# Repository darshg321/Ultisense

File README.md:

# Ultisense

an esp32-s3 devboard made to sense as many things as possible

has:
- an NFC antenna
- 6DOF IMU
- VOC air sensor
- humidity & temperature sensor
- color & ambient light sensor
- magnetometer

it additionally has:
- microphone
- two speakers
- microSD card

## BOM

|Item|Qty                                        |Price (USD)                                |
|----|-------------------------------------------|-------------------------------------------|
|PCB |5                                          |4                                          |
|PCBA|2                                          |161.91                                     |
|Shipping (GSDL)|                                |12.36                                      |

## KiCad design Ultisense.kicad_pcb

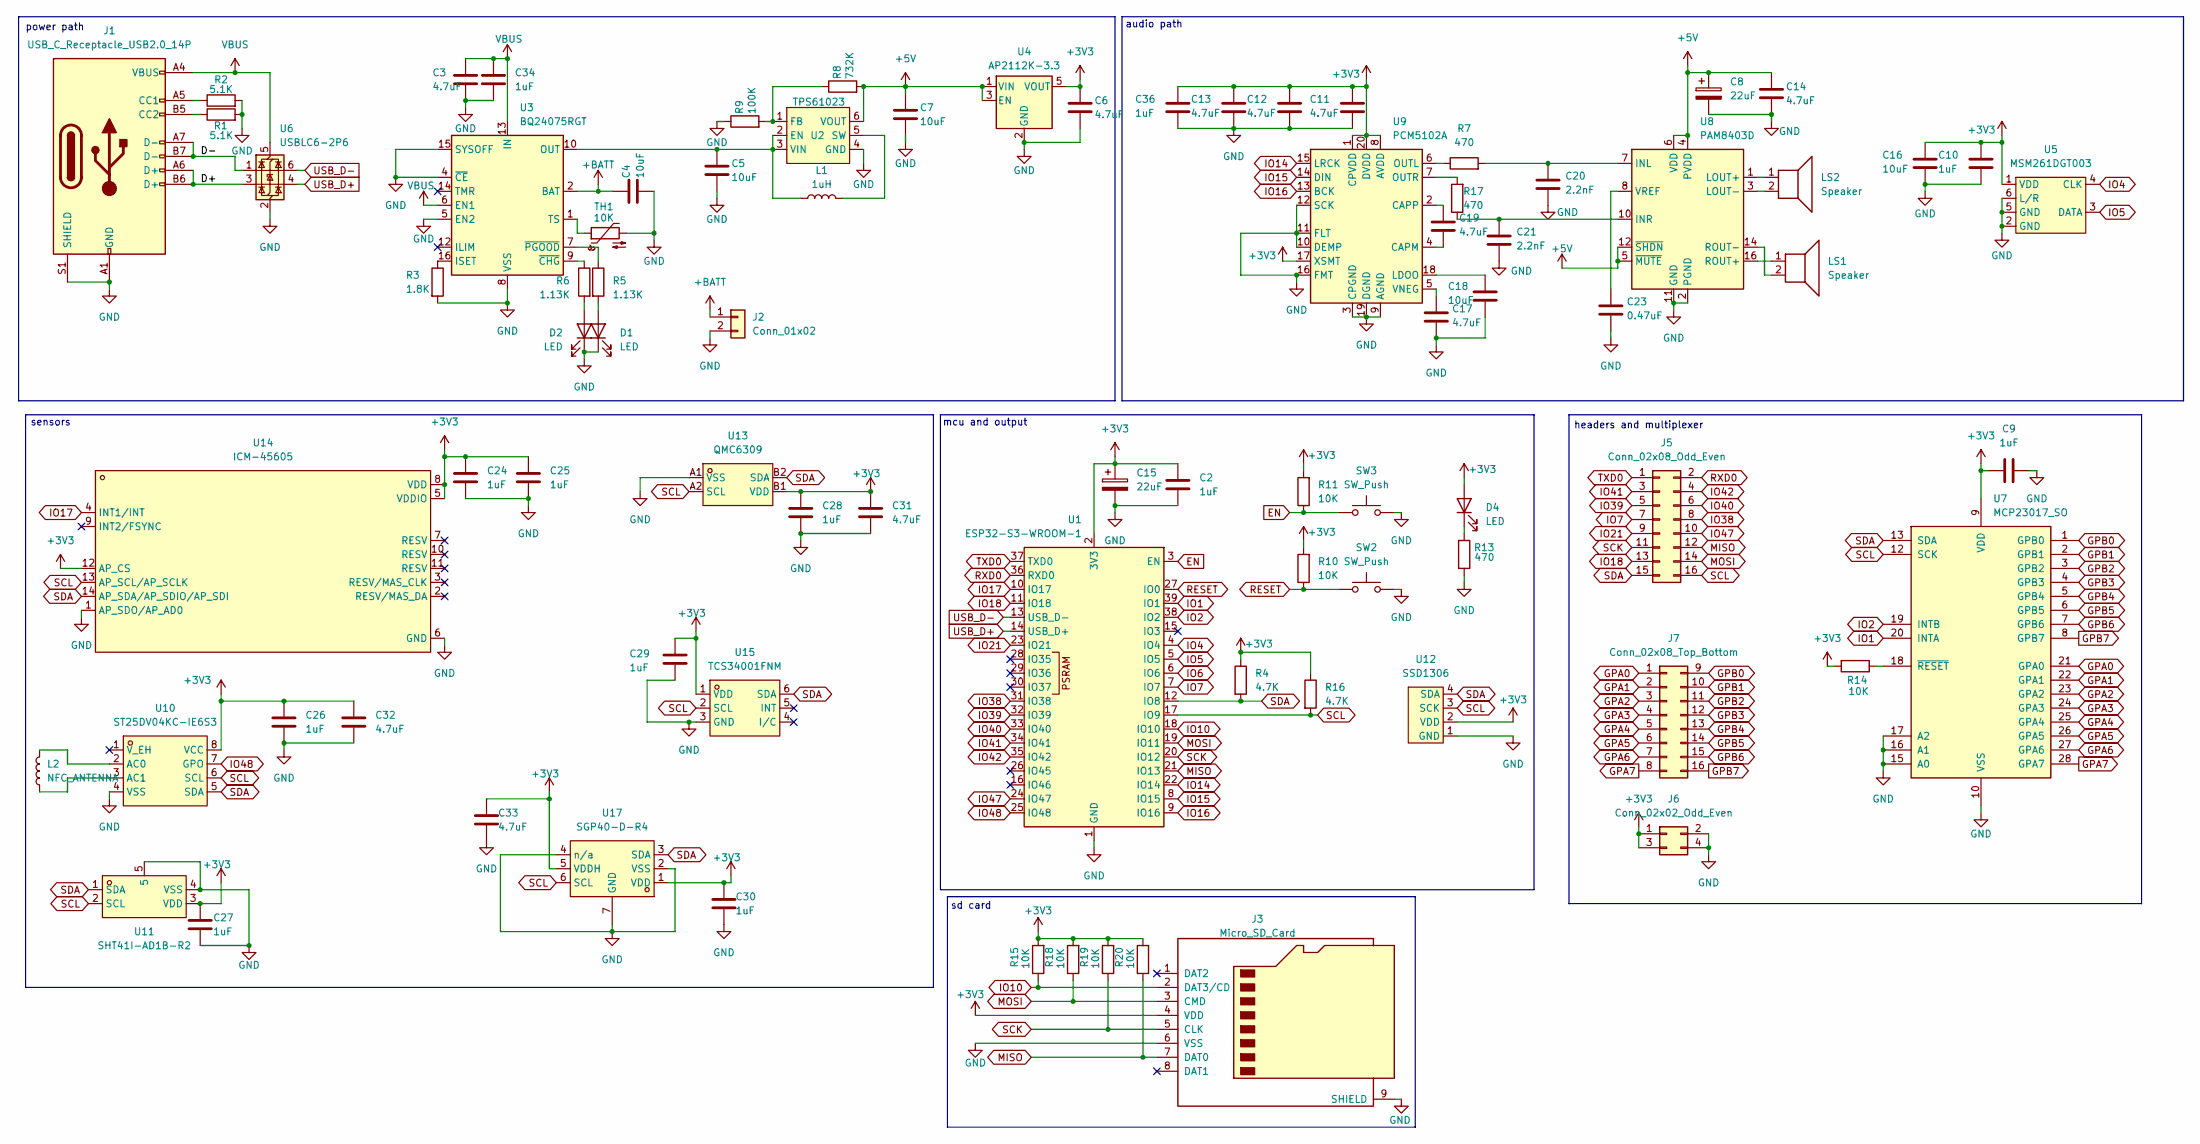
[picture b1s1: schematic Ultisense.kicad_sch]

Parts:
C2, C9, C10, C24, C25, C26, C27, C28, C29, C30, C34, C36: 1uF; C_0201_0603Metric
C3, C6, C11, C12, C13, C14, C17, C19, C31, C32, C33: 4.7uF; C_0201_0603Metric
C4, C5, C7, C16, C18: 10uF; C_0603_1608Metric
C8, C15: 22uF; CP_Elec_4x5.4
C20, C21: 2.2nF; C_0402_1005Metric
C23: 0.47uF; C_0402_1005Metric
D1, D2, D4: LED; LED_0603_1608Metric
J1: USB_C_Receptacle_USB2.0_14P; USB_C_Receptacle_HRO_TYPE-C-31-M-12
J2: Conn_01x02; PinHeader_1x02_P2.54mm_Vertical
J3: Micro_SD_Card; TF-SMD_TF-PUSH
J5: Conn_02x08_Odd_Even; PinHeader_2x08_P2.54mm_Vertical
J6: Conn_02x02_Odd_Even; PinHeader_2x02_P2.54mm_Vertical
J7: Conn_02x08_Top_Bottom; PinSocket_2x08_P2.54mm_Vertical
L1: 1uH; IND-SMD_L4.0-W4.0-A
L2: NFC_ANTENNA; NFC_Coil
LS1, LS2: Speaker; PinHeader_2x01_P2.54mm_Vertical
R1, R2: 5.1K; R_0201_0603Metric
R3: 1.8K; R_0201_0603Metric
R4, R16: 4.7K; R_0201_0603Metric
R5, R6: 1.13K; R_0201_0603Metric
R7, R13, R17: 470; R_0201_0603Metric
R8: 732K; R_0201_0603Metric
R9: 100K; R_0201_0603Metric
R10, R11, R14, R15, R18, R19, R20: 10K; R_0201_0603Metric
SW2, SW3: SW_Push; SW-SMD_L3.9-W3.0-P4.45
TH1: 10K; R_0603_1608Metric
U1: ESP32-S3-WROOM-1
U2: TPS61023; SOT-563_L1.6-W1.2-P0.50-LS1.6-BR
U3: BQ24075RGT; VQFN-16-1EP_3x3mm_P0.5mm_EP1.6x1.6mm
U4: AP2112K-3.3; SOT-23-5
U5: MSM261DGT003; MIC-SMD_6P-L4.0-W2.0_LMD4020T261-OC3
U6: USBLC6-2P6; SOT-666
U7: MCP23017_SO; SOIC-28W_7.5x17.9mm_P1.27mm
U8: PAM8403D; SOP-16_3.9x9.9mm_P1.27mm
U9: PCM5102A; TSSOP-20_4.4x6.5mm_P0.65mm
U10: ST25DV04KC-IE6S3; SO-8_L4.9-W3.9-P1.27-LS5.9-BL; LCSC Part C3304276
U11: SHT41I-AD1B-R2; SENSOR-SMD_4P-L1.5-W1.5-P1.00-TL; LCSC Part C3664410
U12: SSD1306
U13: QMC6309; X1-WLB0808-4_L0.8-W0.8-P0.40-TL; LCSC Part C5439871
U14: ICM-45605; LGA-14_L3.0-W2.5-P0.50-TL; LCSC Part C38673635
U15: TCS34001FNM; DFN-6_L2.4-W2.0-P0.65-BL; LCSC Part C2153593
U17: SGP40-D-R4; DFN-6_L2.4-W2.4-P0.80-TL-EP; LCSC Part C2874215

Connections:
+3V3: C2.2, C6.1, C9.1, C10.1, C11.1, C12.1, C13.1, C15.1, C16.1, C24.1, C25.1, C26.2, C27.2, C28.2, C29.2, C30.2, C31.2, C32.2, C33.2, C36.1, D4.2 (A), J3.4 (VDD), J6.1, J6.3, R4.1, R10.2, R11.2, R14.2, R15.2, R16.1, R18.2, R19.2, R20.2, U1.2 (3V3), U4.5 (VOUT), U5.1 (VDD), U7.9 (VDD), U9.1 (CPVDD), U9.8 (AVDD), U9.17 (XSMT), U9.20 (DVDD), U10.8 (VCC), U11.3 (VDD), U12.2 (VDD), U13.B1 (VDD), U14.5 (VDDIO), U14.8 (VDD), U14.12 (AP_CS), U15.1 (VDD), U17.1 (VDD), U17.5 (VDDH); also elsewhere on the board
+5V: C7.1, C8.1, C14.1, R8.2, U2.6 (VOUT), U4.1 (VIN), U4.3 (EN), U8.4 (PVDD), U8.5 (~MUTE), U8.6 (VDD), U8.12 (~SHDN), U8.13 (PVDD); also elsewhere on the board
+BATT: C4.1, J2.1, U3.2 (BAT), U3.3 (BAT)
/D+: J1.A6 (D+), J1.B6 (D+), U6.3 (I/O2); also elsewhere on the board
/D-: J1.A7 (D-), J1.B7 (D-), U6.1 (I/O1); also elsewhere on the board
EN: R11.1, SW3.1, U1.3 (EN)
GND: C2.1, C3.2, C4.2, C5.2, C6.2, C7.2, C8.2, C9.2, C10.2, C11.2, C12.2, C13.2, C14.2, C15.2, C16.2, C17.2, C18.2, C20.2, C21.2, C23.2, C24.2, C25.2, C26.1, C27.1, C28.1, C29.1, C30.1, C31.1, C32.1, C33.1, C34.2, C36.2, D1.1 (K), D2.1 (K), J1.A1 (GND), J1.A12 (GND), J1.B1 (GND), J1.B12 (GND), J1.S1 (SHIELD), J2.2, J3.6 (VSS), J3.9 (SHIELD), J6.2, J6.4, R1.2, R2.2, R3.2, R9.1, R13.2, SW2.2, SW3.2, TH1.2, U1.1 (GND), U1.40 (GND), U1.41 (GND), U2.4 (GND), U3.4 (~CE), U3.5 (EN2), U3.8 (VSS), U3.15 (SYSOFF), U3.17 (VSS), U4.2 (GND), U5.2 (GND), U5.5 (GND), U5.6 (L/R), U6.2 (GND), U7.10 (VSS), U7.15 (A0), U7.16 (A1), U7.17 (A2), U8.2 (PGND), U8.11 (GND), U8.15 (PGND), U9.3 (CPGND), U9.9 (AGND), U9.10 (DEMP), U9.11 (FLT), U9.12 (SCK), U9.16 (FMT), U9.19 (DGND), U10.4 (VSS), U11.4 (VSS), U11.5, U12.1 (GND), U13.A1 (VSS), U14.1 (AP_SDO/AP_AD0), U14.6 (GND), U15.3 (GND), U17.2 (VSS), U17.4 (n/a), U17.7 (GND)
GPA0: J7.1, U7.21 (GPA0)
GPA1: J7.2, U7.22 (GPA1)
GPA2: J7.3, U7.23 (GPA2)
GPA3: J7.4, U7.24 (GPA3)
GPA4: J7.5, U7.25 (GPA4)
GPA5: J7.6, U7.26 (GPA5)
GPA6: J7.7, U7.27 (GPA6)
GPA7: J7.8, U7.28 (GPA7)
GPB0: J7.9, U7.1 (GPB0)
GPB1: J7.10, U7.2 (GPB1)
GPB2: J7.11, U7.3 (GPB2)
GPB3: J7.12, U7.4 (GPB3)
GPB4: J7.13, U7.5 (GPB4)
GPB5: J7.14, U7.6 (GPB5)
GPB6: J7.15, U7.7 (GPB6)
GPB7: J7.16, U7.8 (GPB7)
IO1: U1.39 (IO1), U7.20 (INTA)
IO2: U1.38 (IO2), U7.19 (INTB)
IO4: U1.4 (IO4), U5.4 (CLK); also elsewhere on the board
IO5: U1.5 (IO5), U5.3 (DATA); also elsewhere on the board
IO6: U1.6 (IO6); also elsewhere on the board
IO7: J5.7, U1.7 (IO7)
IO10: J3.2 (DAT3/CD), R15.1, U1.18 (IO10)
IO14: U1.22 (IO14), U9.15 (LRCK)
IO15: U1.8 (IO15), U9.14 (DIN)
IO16: U1.9 (IO16), U9.13 (BCK)
IO17: U1.10 (IO17), U14.4 (INT1/INT); also elsewhere on the board
IO18: J5.13, U1.11 (IO18)
IO21: J5.9, U1.23 (IO21)
IO38: J5.8, U1.31 (IO38)
IO39: J5.5, U1.32 (IO39)
IO40: J5.6, U1.33 (IO40)
IO41: J5.3, U1.34 (IO41)
IO42: J5.4, U1.35 (IO42)
IO47: J5.10, U1.24 (IO47)
IO48: U1.25 (IO48), U10.7 (GPO); also elsewhere on the board
MISO: J3.7 (DAT0), J5.12, R20.1, U1.21 (IO13)
MOSI: J3.3 (CMD), J5.14, R18.1, U1.19 (IO11)
unnamed: D1.2 (A), R5.2
unnamed: D2.2 (A), R6.2
unnamed: D4.1 (K), R13.1
unnamed: J1.A5 (CC1), R2.1
unnamed: J1.B5 (CC2), R1.1
unnamed: C5.1, L1.1, U2.2 (EN), U2.3 (VIN), U3.10 (OUT), U3.11 (OUT)
unnamed: R8.1, R9.2, U2.1 (FB)
unnamed: L1.2, U2.5 (SW)
unnamed: R3.1, U3.16 (ISET)
unnamed: TH1.1, U3.1 (TS)
unnamed: R6.1, U3.9 (~CHG)
unnamed: R5.1, U3.7 (~PGOOD)
unnamed: R14.1, U7.18 (~RESET)
unnamed: C20.1, R7.2, U8.7 (INL)
unnamed: C21.1, R17.1, U8.10 (INR)
unnamed: LS2.1, U8.1 (LOUT+)
unnamed: LS2.2, U8.3 (LOUT-)
unnamed: LS1.1, U8.16 (ROUT+)
unnamed: LS1.2, U8.14 (ROUT-)
unnamed: C23.1, U8.8 (VREF)
unnamed: C19.2, U9.4 (CAPM)
unnamed: C19.1, U9.2 (CAPP)
unnamed: C18.1, U9.18 (LDOO)
unnamed: R7.1, U9.6 (OUTL)
unnamed: R17.2, U9.7 (OUTR)
unnamed: C17.1, U9.5 (VNEG)
unnamed: L2.2, U10.2 (AC0)
unnamed: L2.1, U10.3 (AC1)
RESET: R10.1, SW2.1, U1.27 (IO0)
RXD0: J5.2, U1.36 (RXD0)
SCK: J3.5 (CLK), J5.11, R19.1, U1.20 (IO12)
SCL: J5.16, R16.2, U1.17 (IO9), U7.12 (SCK), U10.6 (SCL), U11.2 (SCL), U12.3 (SCK), U13.A2 (SCL), U14.13 (AP_SCL/AP_SCLK), U15.2 (SCL), U17.6 (SCL)
SDA: J5.15, R4.2, U1.12 (IO8), U7.13 (SDA), U10.5 (SDA), U11.1 (SDA), U12.4 (SDA), U13.B2 (SDA), U14.14 (AP_SDA/AP_SDIO/AP_SDI), U15.6 (SDA), U17.3 (SDA)
TXD0: J5.1, U1.37 (TXD0)
USB_D+: U1.14 (USB_D+), U6.4 (I/O2)
USB_D-: U1.13 (USB_D-), U6.6 (I/O1)
VBUS: C3.1, C34.1, J1.A4 (VBUS), J1.A9 (VBUS), J1.B4 (VBUS), J1.B9 (VBUS), U3.6 (EN1), U3.13 (IN), U6.5 (VBUS); also elsewhere on the board

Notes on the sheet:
headers and multiplexer
sensors
audio path
power path
sd card
mcu and output

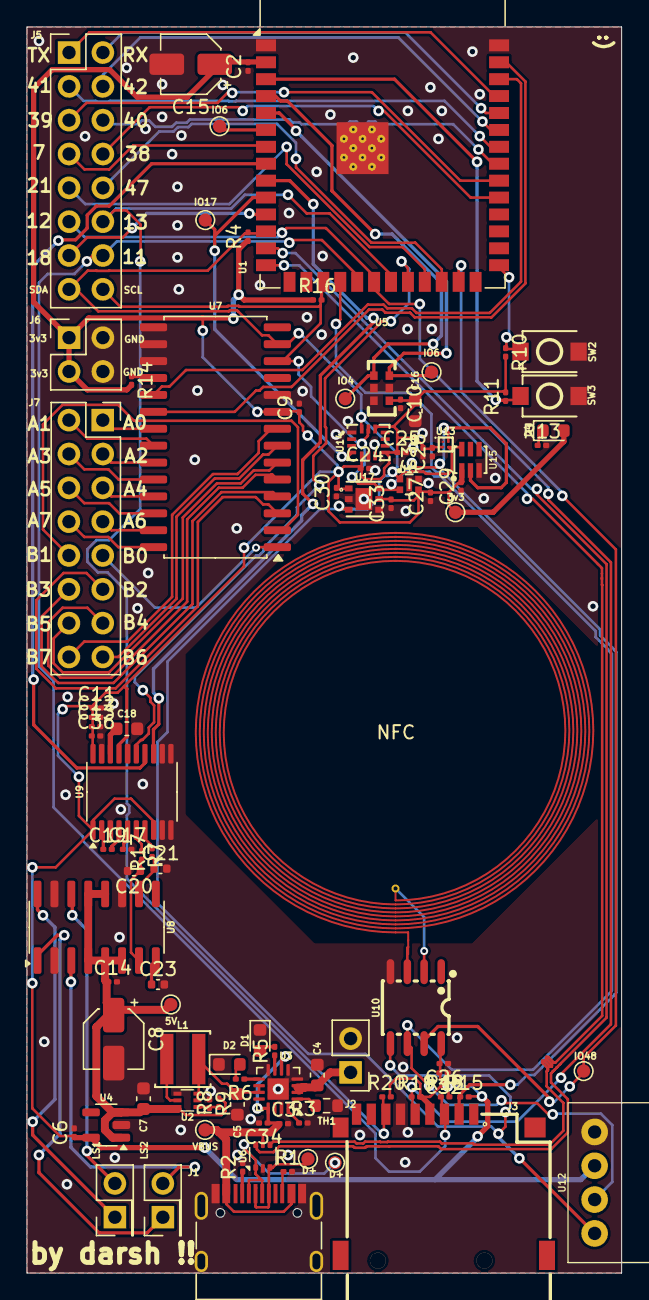
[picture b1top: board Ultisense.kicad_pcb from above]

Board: 2 copper layers, 44.7 x 93.6 mm, 94 parts (0 on the bottom side), 82 nets.

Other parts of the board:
3v3, 5V: TestPoint_Pad_D1.0mm
D+: TestPoint_Pad_D1.0mm
D+#2: TestPoint_Pad_D1.0mm
IO4, IO6, IO6#2, IO17, IO48: TestPoint_Pad_D1.0mm
VBUS: TestPoint_Pad_D1.0mm

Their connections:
+3V3: 3v3.1; also elsewhere on the board
+5V: 5V.1; also elsewhere on the board
/D+: D+.1; also elsewhere on the board
/D-: D+#2.1; also elsewhere on the board
IO4: IO4.1; also elsewhere on the board
IO5: IO6.1; also elsewhere on the board
IO6: IO6#2.1; also elsewhere on the board
IO17: IO17.1; also elsewhere on the board
IO48: IO48.1; also elsewhere on the board
VBUS: VBUS.1; also elsewhere on the board

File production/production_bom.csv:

Designator,Footprint,Quantity,Value,LCSC Part #
"C10, C2, C24, C25, C26, C27, C28, C29, C30, C34, C36, C9",0201,12,1uF,
"C11, C12, C13, C14, C17, C19, C3, C31, C32, C33, C6",0201,11,4.7uF,
"C15, C8",CP_Elec_4x5.4,2,22uF,
"C16, C18, C4, C5, C7",0603,5,10uF,
"C20, C21",0402,2,2.2nF,
C23,0402,1,0.47uF,
"D1, D2, D4",0603,3,LED,
J1,USB_C_Receptacle_HRO_TYPE-C-31-M-12,1,USB_C_Receptacle_USB2.0_14P,
J2,PinHeader_1x02_P2.54mm_Vertical,1,Conn_01x02,
J3,TF-SMD_TF-PUSH,1,Micro_SD_Card,
J5,PinHeader_2x08_P2.54mm_Vertical,1,Conn_02x08_Odd_Even,
J6,PinHeader_2x02_P2.54mm_Vertical,1,Conn_02x02_Odd_Even,
J7,PinSocket_2x08_P2.54mm_Vertical,1,Conn_02x08_Top_Bottom,
L1,IND-SMD_L4.0-W4.0-A,1,1uH,
"LS1, LS2",PinHeader_2x01_P2.54mm_Vertical,2,Speaker,
"R1, R2",0201,2,5.1K,
"R10, R11, R14, R15, R18, R19, R20",0201,7,10K,
"R13, R17, R7",0201,3,470,
"R16, R4",0201,2,4.7K,
R3,0201,1,1.8K,
"R5, R6",0201,2,1.13K,
R8,0201,1,732K,
R9,0201,1,100K,
"SW2, SW3",SW-SMD_L3.9-W3.0-P4.45,2,SW_Push,
TH1,0603,1,10K,
U1,ESP32-S3-WROOM-1,1,ESP32-S3-WROOM-1,
U10,SO-8_L4.9-W3.9-P1.27-LS5.9-BL,1,ST25DV04KC-IE6S3,C3304276
U11,SENSOR-SMD_4P-L1.5-W1.5-P1.00-TL,1,SHT41I-AD1B-R2,C3664410
U12,SSD1306,1,SSD1306,
U13,X1-WLB0808-4_L0.8-W0.8-P0.40-TL,1,QMC6309,C5439871
U14,LGA-14_L3.0-W2.5-P0.50-TL,1,ICM-45605,C38673635
U15,DFN-6_L2.4-W2.0-P0.65-BL,1,TCS34001FNM,C2153593
U17,DFN-6_L2.4-W2.4-P0.80-TL-EP,1,SGP40-D-R4,C2874215
U2,SOT-563_L1.6-W1.2-P0.50-LS1.6-BR,1,TPS61023,
U3,VQFN-16-1EP_3x3mm_P0.5mm_EP1.6x1.6mm,1,BQ24075RGT,
U4,SOT-23-5,1,AP2112K-3.3,
U5,MIC-SMD_6P-L4.0-W2.0_LMD4020T261-OC3,1,MSM261DGT003,
U6,SOT-666,1,USBLC6-2P6,
U7,SOIC-28W_7.5x17.9mm_P1.27mm,1,MCP23017_SO,
U8,SOP-16_3.9x9.9mm_P1.27mm,1,PAM8403D,
U9,TSSOP-20_4.4x6.5mm_P0.65mm,1,PCM5102A,

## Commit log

2025-11-10 mcu + power path + multiplexer + sd card
2025-11-23 finished schematic, starting pcb
2025-11-25 actually fr done schematic, figured out nfc antenna
2025-11-26 layout done
2025-11-28 routing almost done; backup:
2025-11-28 routing done !!
2025-11-28 done
2025-11-29 headers silkscreen
2025-11-30 added test points and changed silkscreen
2025-12-02 fixed nfc
2025-12-02 clean
2025-12-07 replaced out of stock light sensor
2025-12-07 updated assets
2025-12-10 testing firmware
2025-12-11 moved csv
2025-12-14 moved bom yet again
2026-01-02 replaced 01005 with 0201, fixed a few other things, reordering
2026-02-11 build and firmware for sgp40
2026-02-11 update journal
2026-02-24 added sht41I
2026-02-24 added TCS3400
2026-02-24 added QMC6309
